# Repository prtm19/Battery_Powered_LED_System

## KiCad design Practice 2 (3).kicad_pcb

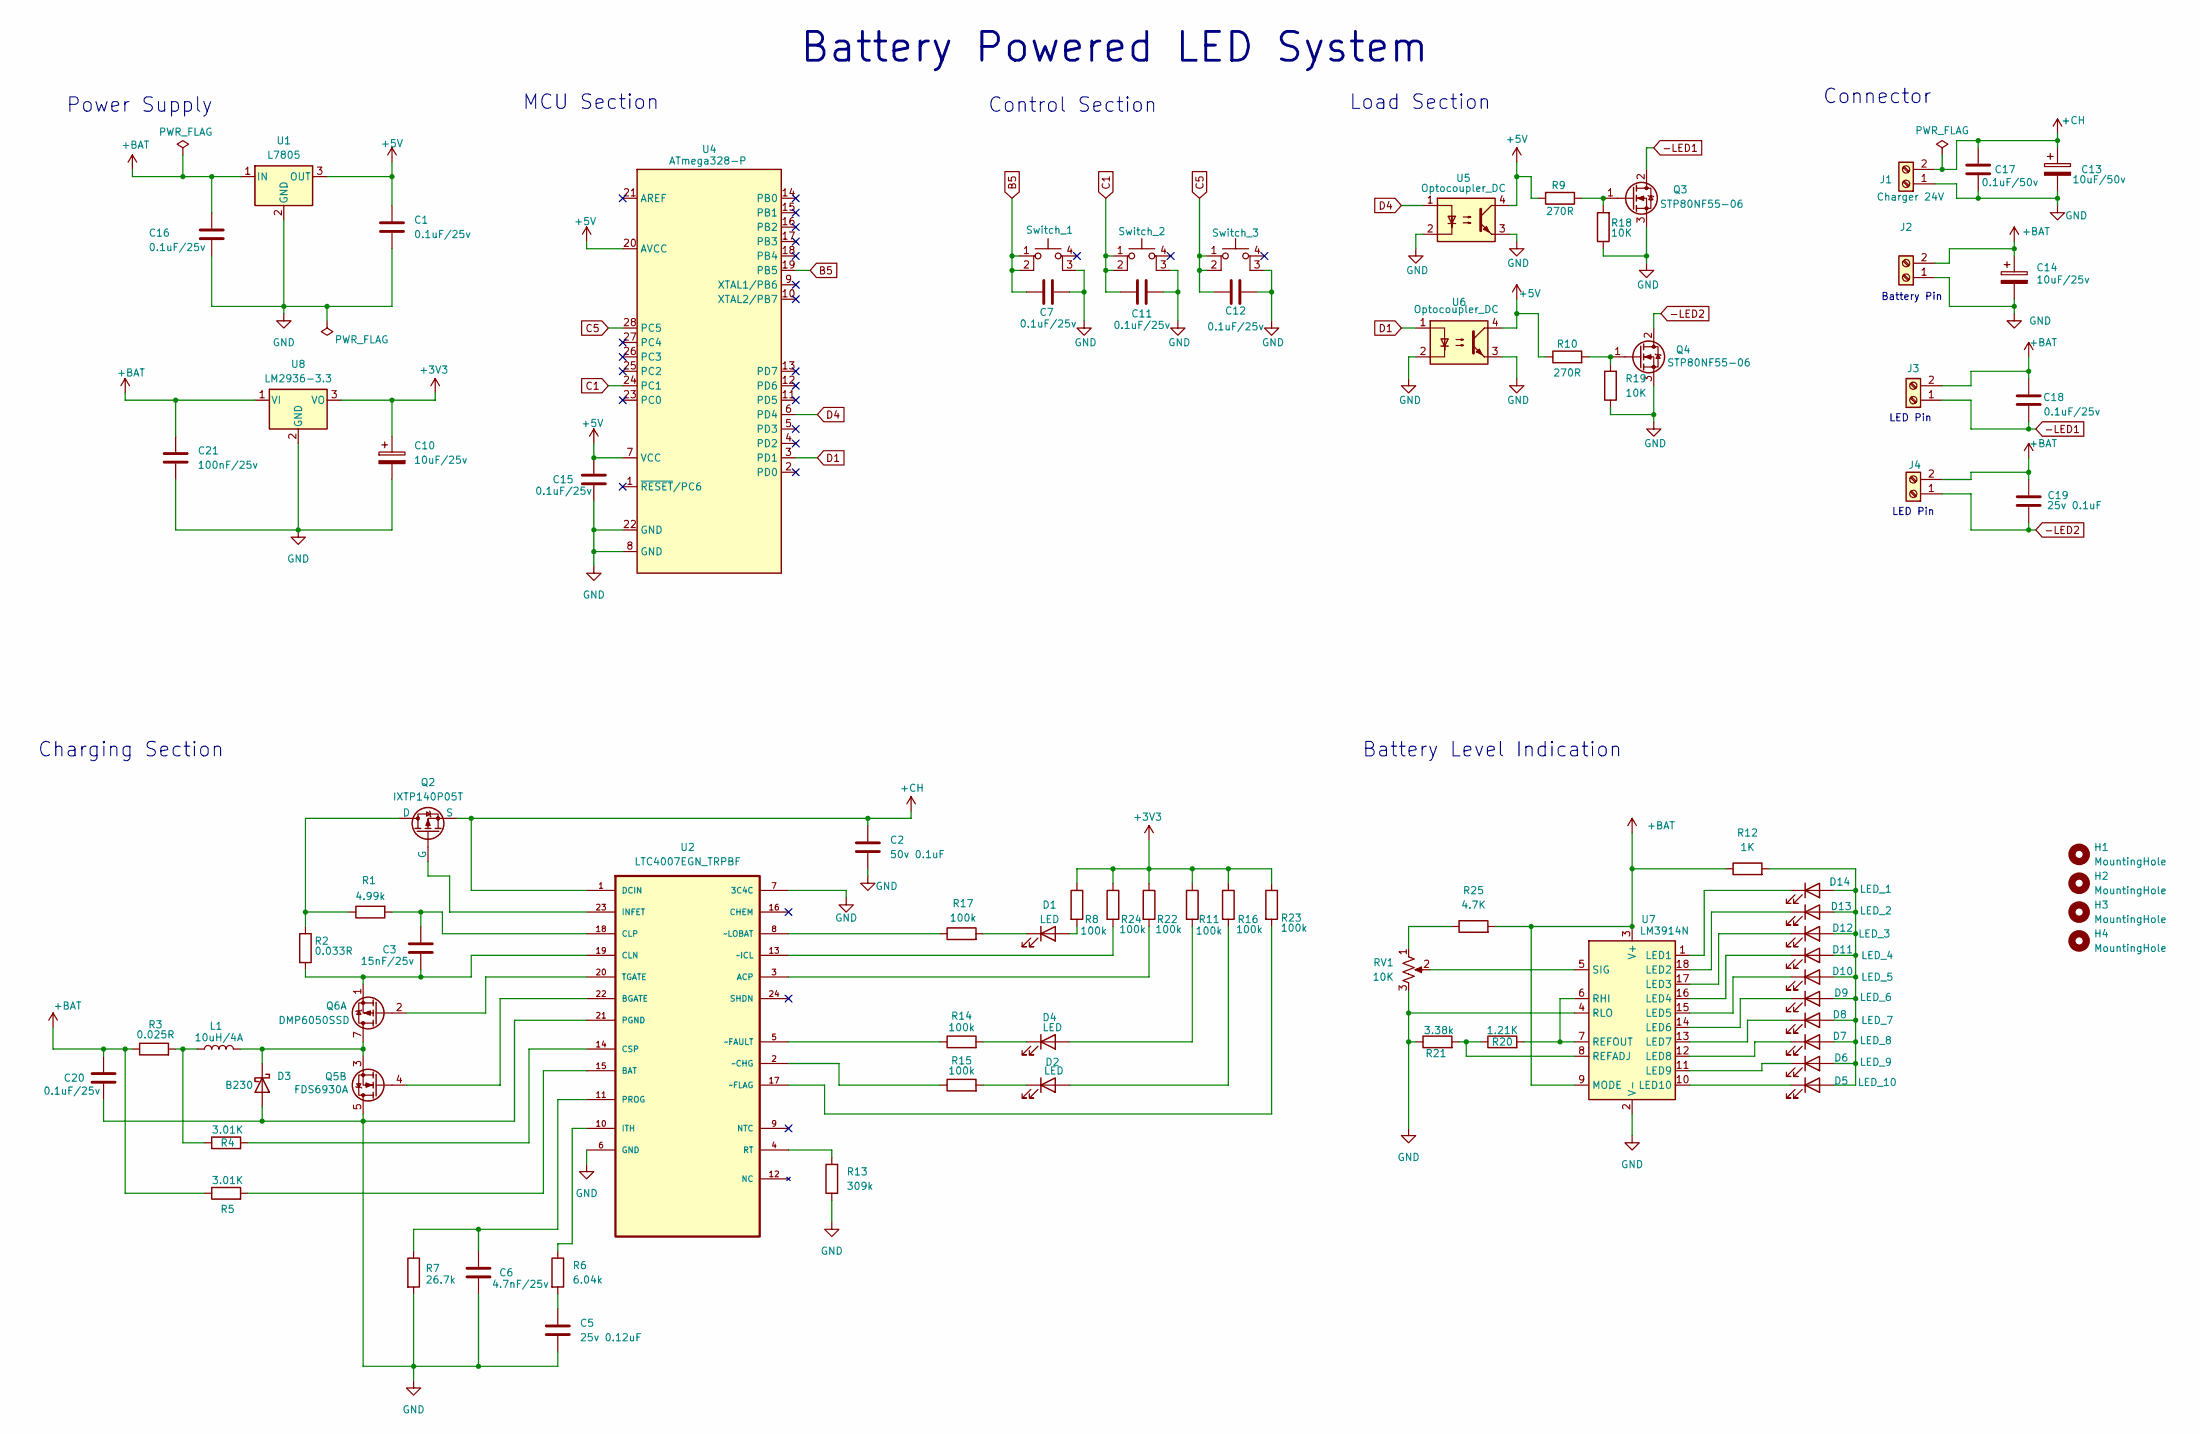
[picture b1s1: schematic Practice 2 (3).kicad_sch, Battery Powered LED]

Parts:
C1, C7, C11, C12, C15, C16, C18, C20: 0.1uF/25v; C_0805_2012Metric_Pad1.18x1.45mm_HandSolder
C2: 50v 0.1uF; C_0805_2012Metric_Pad1.18x1.45mm_HandSolder
C3: 15nF/25v; C_0805_2012Metric_Pad1.18x1.45mm_HandSolder
C5: 25v 0.12uF; C_0805_2012Metric_Pad1.18x1.45mm_HandSolder
C6: 4.7nF/25v; C_0805_2012Metric_Pad1.18x1.45mm_HandSolder
C10, C14: 10uF/25v; CP_Radial_D5.0mm_P2.00mm
C13: 10uF/50v; CP_Radial_D5.0mm_P2.00mm
C17: 0.1uF/50v; C_0805_2012Metric_Pad1.18x1.45mm_HandSolder
C19: 25v 0.1uF; C_0805_2012Metric_Pad1.18x1.45mm_HandSolder
C21: 100nF/25v; C_0805_2012Metric_Pad1.18x1.45mm_HandSolder
D1, D2, D4: LED; LED_0805_2012Metric_Pad1.15x1.40mm_HandSolder
D3: B230; D_SMB
D5: LED_10; LED_0805_2012Metric_Pad1.15x1.40mm_HandSolder
D6: LED_9; LED_0805_2012Metric_Pad1.15x1.40mm_HandSolder
D7: LED_8; LED_0805_2012Metric_Pad1.15x1.40mm_HandSolder
D8: LED_7; LED_0805_2012Metric_Pad1.15x1.40mm_HandSolder
D9: LED_6; LED_0805_2012Metric_Pad1.15x1.40mm_HandSolder
D10: LED_5; LED_0805_2012Metric_Pad1.15x1.40mm_HandSolder
D11: LED_4; LED_0805_2012Metric_Pad1.15x1.40mm_HandSolder
D12: LED_3; LED_0805_2012Metric_Pad1.15x1.40mm_HandSolder
D13: LED_2; LED_0805_2012Metric_Pad1.15x1.40mm_HandSolder
D14: LED_1; LED_0805_2012Metric_Pad1.15x1.40mm_HandSolder
H1, H2, H3, H4: MountingHole; MountingHole_3.5mm
J1, J2, J3, J4: Screw_Terminal_01x02; PhoenixContact_MCV_1,5_2-G-3.81_1x02_P3.81mm_Vertical
L1: 10uH/4A; L_APV_APH0530
Q2: IXTP140P05T; TO-220-3_Vertical
Q3, Q4: STP80NF55-06; TO-220-3_Vertical
Q5: FDS6930A; SOIC-8_3.9x4.9mm_P1.27mm
Q6: DMP6050SSD; SOIC-8_3.9x4.9mm_P1.27mm
R1: 4.99k; R_0805_2012Metric_Pad1.20x1.40mm_HandSolder
R2: 0.033R; R_1206_3216Metric_Pad1.30x1.75mm_HandSolder
R3: 0.025R; R_0805_2012Metric_Pad1.20x1.40mm_HandSolder
R4, R5: 3.01K; R_0805_2012Metric_Pad1.20x1.40mm_HandSolder
R6: 6.04k; R_0805_2012Metric_Pad1.20x1.40mm_HandSolder
R7: 26.7k; R_0805_2012Metric_Pad1.20x1.40mm_HandSolder
R8, R11, R14, R15, R16, R17, R22, R23, R24: 100k; R_0805_2012Metric_Pad1.20x1.40mm_HandSolder
R9, R10: 270R; R_0805_2012Metric_Pad1.20x1.40mm_HandSolder
R12: 1K; R_0805_2012Metric_Pad1.20x1.40mm_HandSolder
R13: 309k; R_0805_2012Metric_Pad1.20x1.40mm_HandSolder
R18, R19: 10K; R_0805_2012Metric_Pad1.20x1.40mm_HandSolder
R20: 1.21K; R_0805_2012Metric_Pad1.20x1.40mm_HandSolder
R21: 3.38k; R_0805_2012Metric_Pad1.20x1.40mm_HandSolder
R25: 4.7K; R_0805_2012Metric_Pad1.20x1.40mm_HandSolder
RV1: 10K; Potentiometer_Bourns_3296W_Vertical
Switch_1, Switch_2, Switch_3: SW_Push_2P1T_Toggle_CK_PVA1xxH1xxxxxxV2
U1: L7805; TO-220-3_Vertical
U2: LTC4007EGN_TRPBF; SOP63P600X175-24N; MPN LTC4007EGN#PBF; DigiKey_Part_Number LTC4007EGN#TRPBFCT-ND
U4: ATmega328-P; DIP-28_W7.62mm_LongPads
U5, U6: Optocoupler_DC; DIP-4_W7.62mm
U7: LM3914N; DIP-18_W7.62mm_SMDSocket_SmallPads
U8: LM2936-3.3; SOT-223

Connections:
+3V3: C10.1, R8.1, R11.1, R16.1, R22.1, R23.1, R24.1, U8.3 (VO)
+5V: C1.1, C15.1, R9.2, R10.1, U1.3 (OUT), U4.7 (VCC), U4.20 (AVCC), U5.4, U6.4
+BAT: C14.1, C16.1, C18.1, C19.1, C20.1, C21.1, J2.2, J3.2, J4.2, R3.1, R5.1, R12.1, R25.2, U1.1 (IN), U7.3 (V+), U7.9 (MODE), U8.1 (VI)
+CH: C2.1, C13.1, C17.1, J1.2, Q2.3 (S), U2.1 (DCIN)
-LED1: C18.2, J3.1, Q3.2 (D)
-LED2: C19.2, J4.1, Q4.2 (D)
B5: C7.1, Switch_1.1, Switch_1.2, U4.19 (PB5)
C1: C11.1, Switch_2.1, Switch_2.2, U4.24 (PC1)
C5: C12.1, Switch_3.1, Switch_3.2, U4.28 (PC5)
D1: U4.3 (PD1), U6.1
D4: U4.6 (PD4), U5.1
GND: C1.2, C2.2, C5.2, C6.2, C7.2, C10.2, C11.2, C12.2, C13.2, C14.2, C15.2, C16.2, C17.2, C20.2, C21.2, D3.2 (A), J1.1, J2.1, Q3.3 (S), Q4.3 (S), Q5.5 (D2), Q5.6 (D2), R7.2, R13.1, R18.1, R19.1, R21.1, RV1.3, Switch_1.3 (K), Switch_2.3 (K), Switch_3.3 (K), U1.2 (GND), U2.6 (GND), U2.7 (3C4C), U2.21 (PGND), U4.8 (GND), U4.22 (GND), U5.2, U5.3, U6.2, U6.3, U7.2 (V-), U7.4 (RLO), U8.2 (GND)
unnamed: C5.1, R6.2
unnamed: D1.2 (A), R8.2
unnamed: D1.1 (K), R17.2
unnamed: D2.2 (A), R16.2
unnamed: D2.1 (K), R15.2
unnamed: D3.1 (K), L1.2, Q5.3 (S2), Q6.7 (D1), Q6.8 (D1)
unnamed: D4.2 (A), R11.2
unnamed: D4.1 (K), R14.2
unnamed: D5.1 (K), U7.10 (LED10)
unnamed: D6.1 (K), U7.11 (LED9)
unnamed: D7.1 (K), U7.12 (LED8)
unnamed: D8.1 (K), U7.13 (LED7)
unnamed: D9.1 (K), U7.14 (LED6)
unnamed: D5.2 (A), D6.2 (A), D7.2 (A), D8.2 (A), D9.2 (A), D10.2 (A), D11.2 (A), D12.2 (A), D13.2 (A), D14.2 (A), R12.2
unnamed: D10.1 (K), U7.15 (LED5)
unnamed: D11.1 (K), U7.16 (LED4)
unnamed: D12.1 (K), U7.17 (LED3)
unnamed: D13.1 (K), U7.18 (LED2)
unnamed: D14.1 (K), U7.1 (LED1)
unnamed: L1.1, R3.2, R4.1
unnamed: Q2.1 (D), R1.1, R2.1
unnamed: Q2.2 (G), U2.23 (INFET)
unnamed: Q3.1 (G), R9.1, R18.2
unnamed: Q4.1 (G), R10.2, R19.2
unnamed: Q5.4 (G2), U2.22 (BGATE)
unnamed: Q6.2 (G1), U2.20 (TGATE)
unnamed: C3.2, Q6.1 (S1), R2.2, U2.19 (CLN)
unnamed: R25.1, RV1.1
unnamed: R22.2, U2.3 (ACP)
unnamed: R5.2, U2.15 (BAT)
unnamed: C3.1, R1.2, U2.18 (CLP)
unnamed: R4.2, U2.14 (CSP)
unnamed: R6.1, U2.10 (ITH)
unnamed: C6.1, R7.1, U2.11 (PROG)
unnamed: R13.2, U2.4 (RT)
unnamed: R15.1, U2.2 (~CHG)
unnamed: R14.1, U2.5 (~FAULT)
unnamed: R23.2, U2.17 (~FLAG)
unnamed: R24.2, U2.13 (~ICL)
unnamed: R17.1, U2.8 (~LOBAT)
unnamed: R20.1, R21.2, U7.8 (REFADJ)
unnamed: R20.2, U7.6 (RHI), U7.7 (REFOUT)
unnamed: RV1.2, U7.5 (SIG)

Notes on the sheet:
Power Supply
LED Pin
Battery Powered LED System
Control Section
Charging Section
Battery Level Indication
MCU Section
LED Pin
Battery Pin
Connector
Load Section

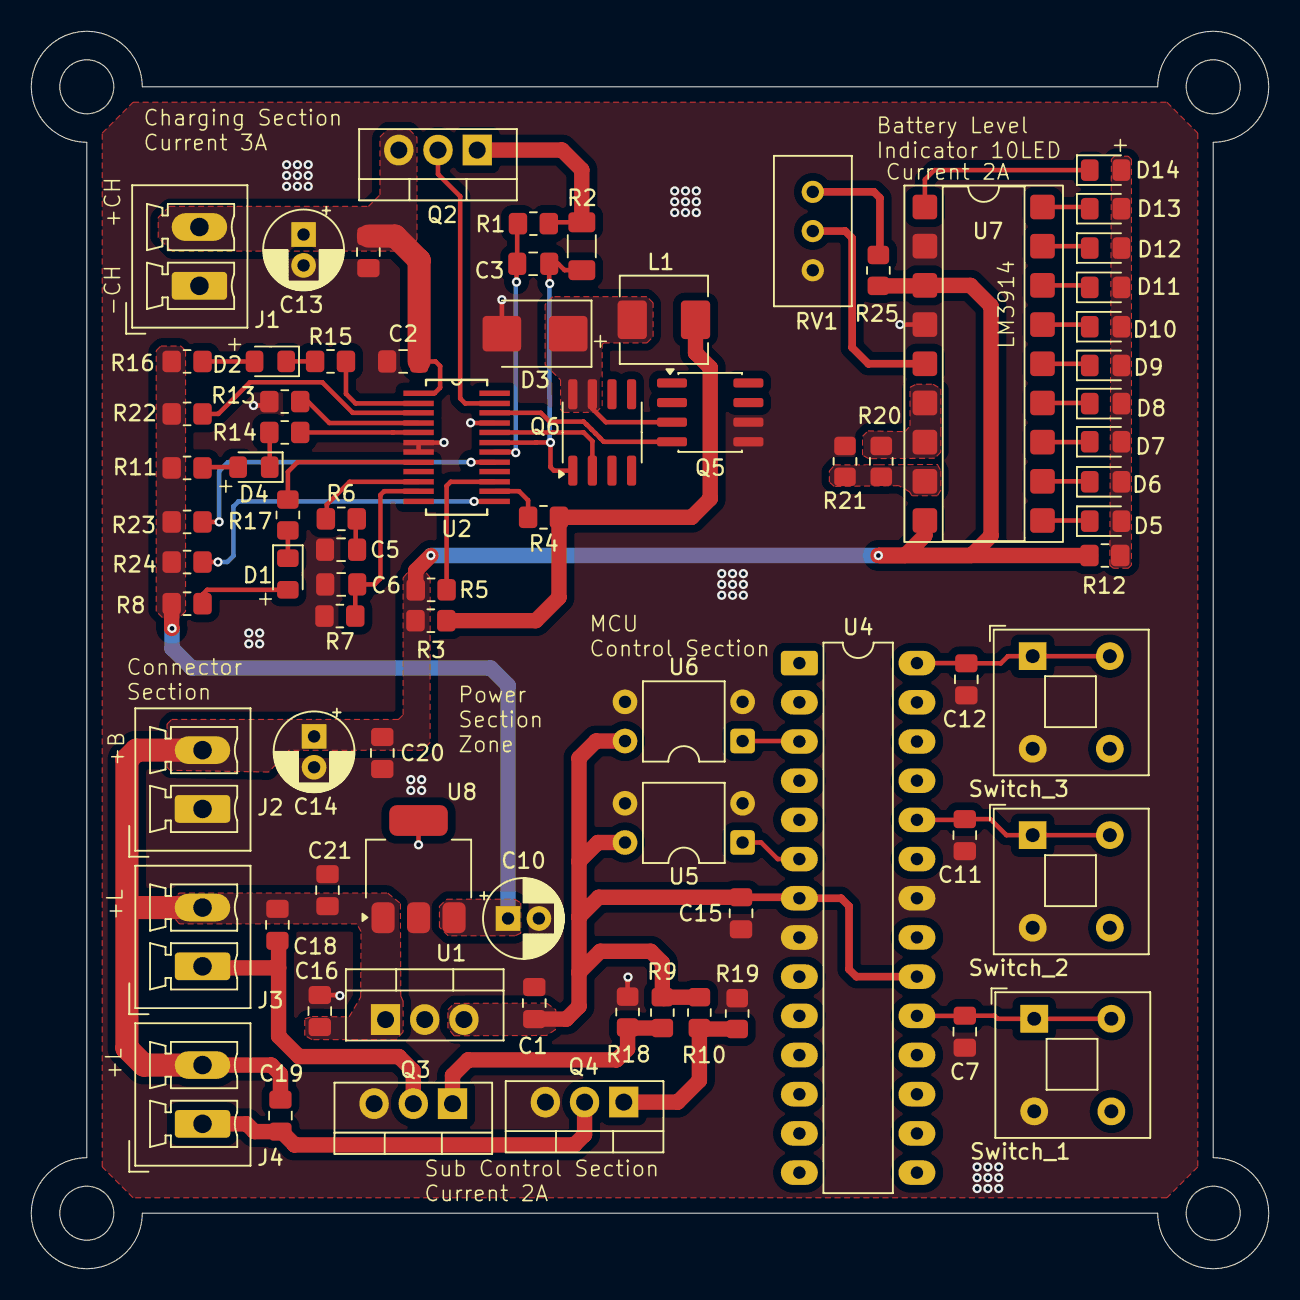
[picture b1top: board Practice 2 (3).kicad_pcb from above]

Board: 2 copper layers, 80.2 x 80.2 mm, 82 parts (0 on the bottom side), 55 nets.

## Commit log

2025-11-16 update file
2025-11-16 Add readme file
